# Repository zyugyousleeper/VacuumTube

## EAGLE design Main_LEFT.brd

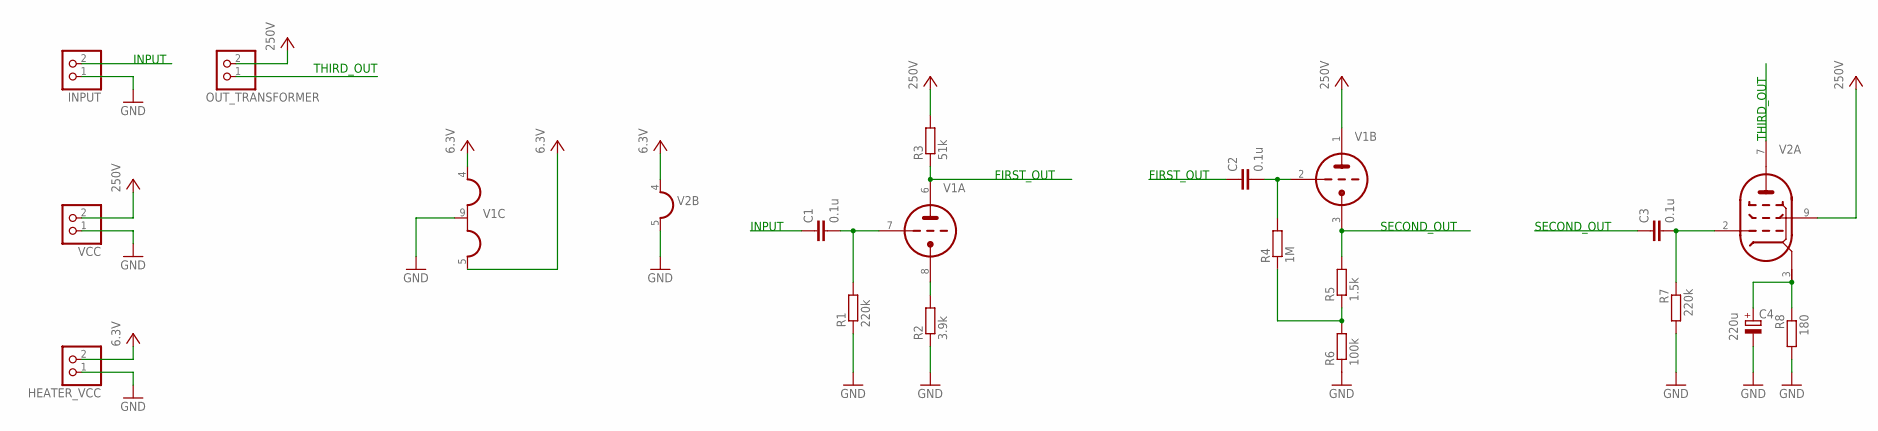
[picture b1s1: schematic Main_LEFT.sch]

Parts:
C1, C2, C3: 0.1u; C025-025X050
C4: 220u; E2,5-6
HEATER_VCC: PINHD-1X2; 1X02
INPUT: PINHD-1X2; 1X02
OUT_TRANSFORMER: PINHD-1X2; 1X02
R1, R7: 220k; 0207/7
R2: 3.9k; 0207/7
R3: 51k; 0207/7
R4: 1M; 0207/7
R5: 1.5k; 0207/7
R6: 100k; 0207/7
R8: 180; 0207/7
V1: AT-MT9P(12AX7); AT-MT9P
V2: AT-MT9P(6BQ5); AT-MT9P
VCC: PINHD-1X2; 1X02

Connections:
GND: C4.-, HEATER_VCC.1, INPUT.1, R1.1, R2.1, R6.1, R7.2, R8.2, V1.9 (H2), V2.5 (H2), VCC.1
unnamed: R3.1, V1.6 (TA)
unnamed: R2.2, V1.8 (TK)
unnamed: C1.2, R1.2, V1.7 (TG)
unnamed: R5.2, V1.3 (TK)
unnamed: R4.1, R5.1, R6.2
unnamed: C2.2, R4.2, V1.2 (TG)
unnamed: C3.2, R7.1, V2.2 (PG)
unnamed: C4.+, R8.1, V2.3 (PK)
VCC: HEATER_VCC.2, OUT_TRANSFORMER.2, R3.2, V1.1 (TA), V1.4 (H1), V1.5 (H3), V2.4 (H1), VCC.2

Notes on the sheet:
INPUT
FIRST_OUT
SECOND_OUT
THIRD_OUT

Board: 2 copper layers, 18 parts (0 on the bottom side), 10 nets, no tracks yet.

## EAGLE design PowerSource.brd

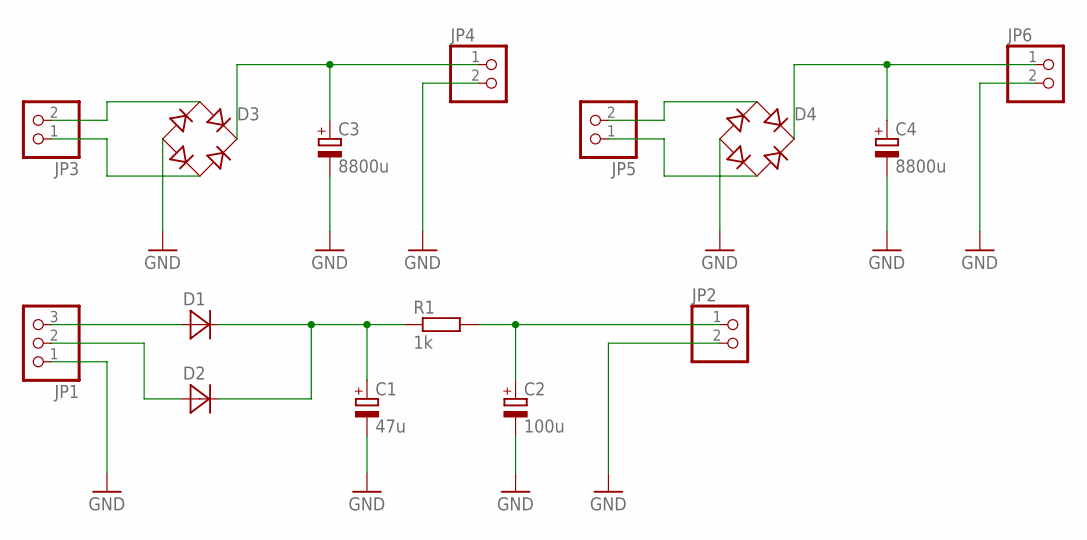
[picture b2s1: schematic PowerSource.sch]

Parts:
C1: 47u; E7,5-16
C2: 100u; E7,5-18
C3, C4: 8800u; E7,5-18
D1, D2: DIODE; DO07
D3, D4: BRIDGERECTIFIER
JP1: PINHD-1X3; 1X03
JP2, JP3, JP4, JP5, JP6: PINHD-1X2; 1X02
R1: 1k; 0207/7

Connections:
GND: C1.-, C2.-, C3.-, C4.-, D3.-, D4.-, JP1.1, JP2.2, JP4.2, JP6.2
unnamed: D2.A, JP1.2
unnamed: D1.A, JP1.3
unnamed: D3.AC1, JP3.2
unnamed: D3.AC2, JP3.1
unnamed: C4.+, D4.+, JP6.1
unnamed: D4.AC1, JP5.2
unnamed: C3.+, D3.+, JP4.1
unnamed: D4.AC2, JP5.1
unnamed: C2.+, JP2.1, R1.2
unnamed: C1.+, D1.C, D2.C, R1.1

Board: 2 copper layers, 15 parts (0 on the bottom side), 11 nets, no tracks yet.

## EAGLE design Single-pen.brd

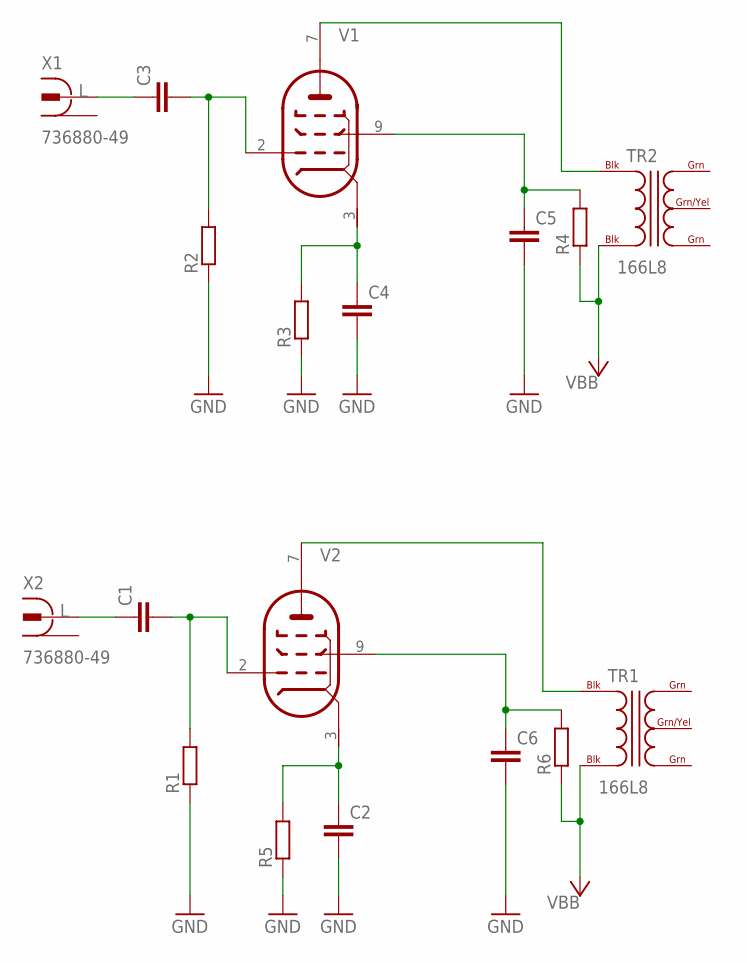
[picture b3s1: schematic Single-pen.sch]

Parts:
C1, C2, C3, C4, C5, C6: C10/5; C10B5
R1, R2, R3, R4, R5, R6: R-EU_0207/5V; 0207/5V
TR1, TR2: 166L8; C8H
V1, V2: 6BQ5-P; NOVAL
X1, X2: 736880-49

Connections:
GND: C2.2, C4.2, C5.2, C6.2, R1.1, R2.1, R3.1, R5.1
unnamed: C2.1, R5.2, V2.3 (PK)
unnamed: C6.1, R6.2, V2.9 (PSG)
unnamed: C3.2, R2.2, V1.2 (PG)
unnamed: C1.2, R1.2, V2.2 (PG)
unnamed: TR2.BLK@1 (BLK), V1.7 (PA)
unnamed: TR1.BLK@1 (BLK), V2.7 (PA)
unnamed: C3.1, X1.2
unnamed: C4.1, R3.2, V1.3 (PK)
unnamed: C5.1, R4.2, V1.9 (PSG)
unnamed: C1.1, X2.2
VCC: R4.1, R6.1, TR1.BLK@2 (BLK), TR2.BLK@2 (BLK)

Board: 2 copper layers, 18 parts (0 on the bottom side), 12 nets, no tracks yet.

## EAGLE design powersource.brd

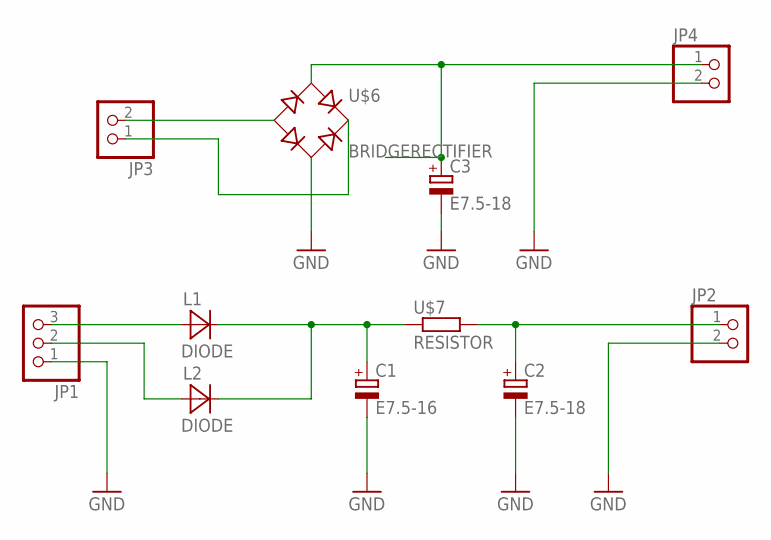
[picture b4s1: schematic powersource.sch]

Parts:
C1: E7.5-16; E7,5-16
C2, C3: E7.5-18; E7,5-18
JP1: PINHD-1X3; 1X03
JP2, JP3, JP4: PINHD-1X2; 1X02
L1, L2: DIODE; DO07
U$6: BRIDGERECTIFIER
U$7: RESISTOR

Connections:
GND: C1.-, C2.-, C3.-, JP1.1, JP2.2, JP4.2, U$6.AC2
unnamed: JP1.2, L2.A
unnamed: JP1.3, L1.A
unnamed: JP3.2, U$6.-
unnamed: JP3.1, U$6.+
unnamed: C3.+, JP4.1, U$6.AC1
unnamed: C2.+, JP2.1, U$7.2
unnamed: C1.+, L1.C, L2.C, U$7.1

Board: 2 copper layers, 11 parts (0 on the bottom side), 8 nets, no tracks yet.

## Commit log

2019-01-21 シングルパワーアンプの回路図作った
2019-01-22 [add]基板
2019-01-22 [add]電源の基板
2019-01-22 Add PowerSourve and PowerSource_for_Heater
2019-01-24 [add]電源回路をいい感じにした
2019-01-24 [rm]dengen.sch
2019-01-24 [fix]超超微調整
2019-01-24 [add]ただの基板を追加
2019-01-24 [add]穴を追加
2019-01-24 [oh...]保存してないでコミットしてpushしてしまっていたかもしれない？
2019-01-24 [add]真空管をのっけた基板を作成
2019-01-27 [fix]真空管の場所を少し変更
2019-01-28 [add]切り欠きをした
2019-01-28 [fix]切り欠きの修正
2019-01-29 Nixie Deign
2019-02-17 [rm]Partsというファイルを消去
2019-02-17 [rm]Nixie.schというファイルを消去
2019-02-17 [add].gitignore
2019-02-17 [rm]真空管アンプ筐体の設計をするために必要だった基板を違うリポジトリに移動した
2019-02-17 [mv]電源回路のファイル達をリネーム
2019-02-17 [mv]真空管アンプのメイン回路をリネーム
2019-02-17 [rm]いったん全部消去
2019-02-17 [add]全回路作成
2019-02-17 [fix]ピンのラベルを編集
2019-02-17 [fix]基板に絶望している
2019-02-17 [fix]電源回路を手直し
2019-02-17 [fix]重大な欠陥を直した
2019-02-17 [fix]重大な欠陥
2019-02-17 [fix]手直し
2019-02-19 [add]pdfを生成
2019-02-19 [fix]電源の重大な欠陥
2019-02-19 [fix]電源の直し
2019-02-20 [fix]スクリーングリッドの抵抗値と容量を変化
2019-02-20 [add]powerのpdfを作成
2019-02-20 [fix]ヒーター電源を二つ使うことにした
2019-02-21 [fix]直し
2019-02-21 [fix]右と左の回路図を分けた
2019-02-21 [fix]右と左分けた
2019-02-21 [fix]ボード作成
